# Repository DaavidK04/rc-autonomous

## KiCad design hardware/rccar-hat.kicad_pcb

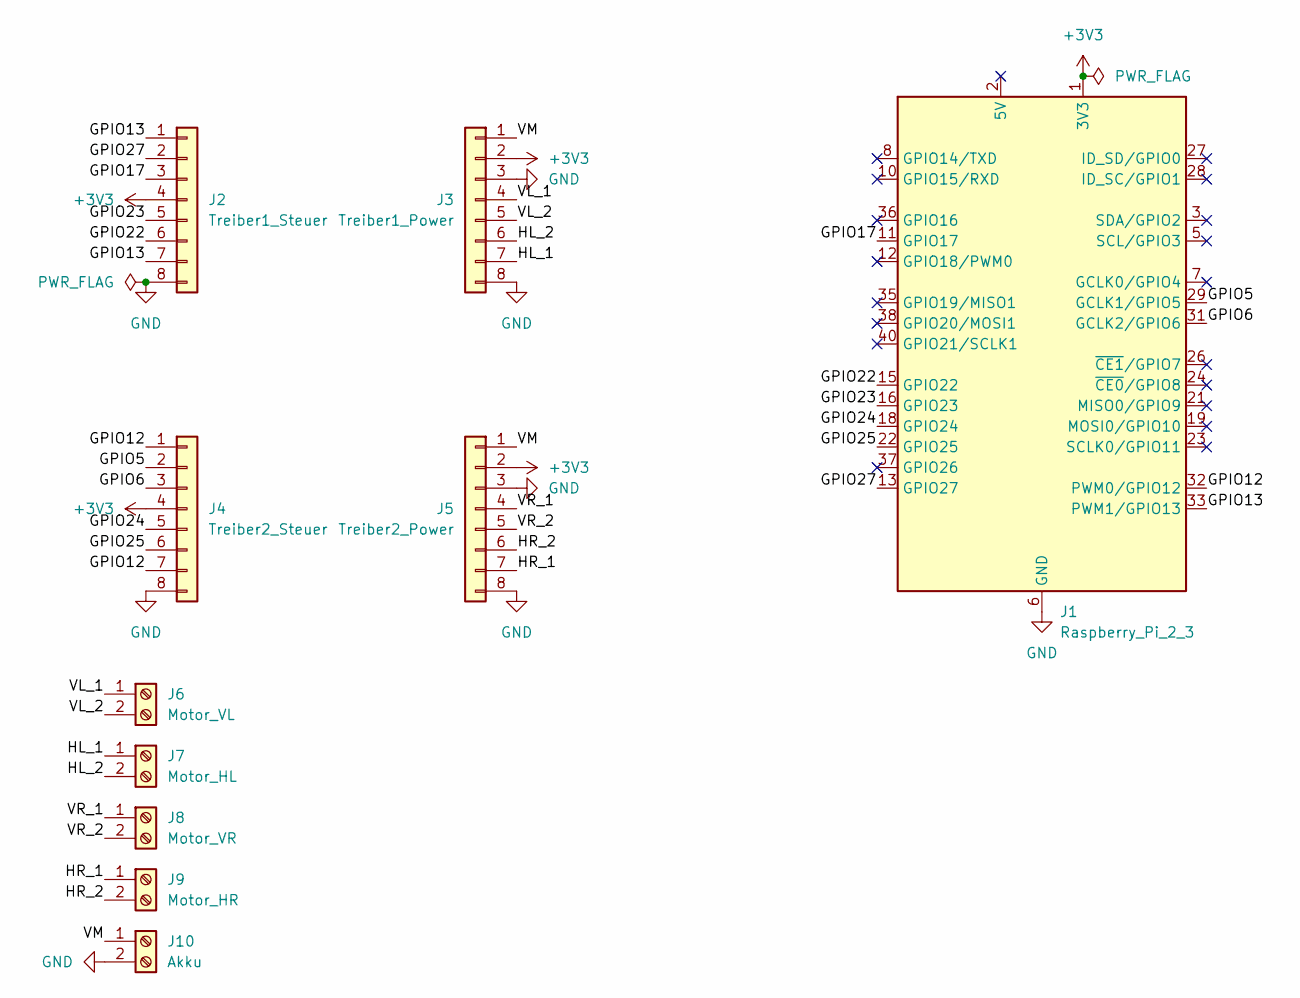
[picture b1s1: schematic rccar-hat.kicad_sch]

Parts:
J1: Raspberry_Pi_2_3; PinSocket_2x20_P2.54mm_Vertical
J2: Treiber1_Steuer; PinSocket_1x08_P2.54mm_Vertical
J3: Treiber1_Power; PinSocket_1x08_P2.54mm_Vertical
J4: Treiber2_Steuer; PinSocket_1x08_P2.54mm_Vertical
J5: Treiber2_Power; PinSocket_1x08_P2.54mm_Vertical
J6: Motor_VL; TerminalBlock_Phoenix_PT-1,5-2-3.5-H_1x02_P3.50mm_Horizontal
J7: Motor_HL; TerminalBlock_Phoenix_PT-1,5-2-3.5-H_1x02_P3.50mm_Horizontal
J8: Motor_VR; TerminalBlock_Phoenix_PT-1,5-2-3.5-H_1x02_P3.50mm_Horizontal
J9: Motor_HR; TerminalBlock_Phoenix_PT-1,5-2-3.5-H_1x02_P3.50mm_Horizontal
J10: Akku; TerminalBlock_Phoenix_PT-1,5-2-3.5-H_1x02_P3.50mm_Horizontal

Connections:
+3V3: J1.1 (3V3), J1.17 (3V3), J2.4, J3.2, J4.4, J5.2
/GPIO5: J1.29 (GCLK1/GPIO5), J4.2
/GPIO6: J1.31 (GCLK2/GPIO6), J4.3
/GPIO12: J1.32 (PWM0/GPIO12), J4.1, J4.7
/GPIO13: J1.33 (PWM1/GPIO13), J2.1, J2.7
/GPIO17: J1.11 (GPIO17), J2.3
/GPIO22: J1.15 (GPIO22), J2.6
/GPIO23: J1.16 (GPIO23), J2.5
/GPIO24: J1.18 (GPIO24), J4.5
/GPIO25: J1.22 (GPIO25), J4.6
/GPIO27: J1.13 (GPIO27), J2.2
/HL_1: J3.7, J7.1
/HL_2: J3.6, J7.2
/HR_1: J5.7, J9.1
/HR_2: J5.6, J9.2
/VL_1: J3.4, J6.1
/VL_2: J3.5, J6.2
/VM: J3.1, J5.1, J10.1
/VR_1: J5.4, J8.1
/VR_2: J5.5, J8.2
GND: J1.6 (GND), J1.9 (GND), J1.14 (GND), J1.20 (GND), J1.25 (GND), J1.30 (GND), J1.34 (GND), J1.39 (GND), J2.8, J3.3, J3.8, J4.8, J5.3, J5.8, J10.2

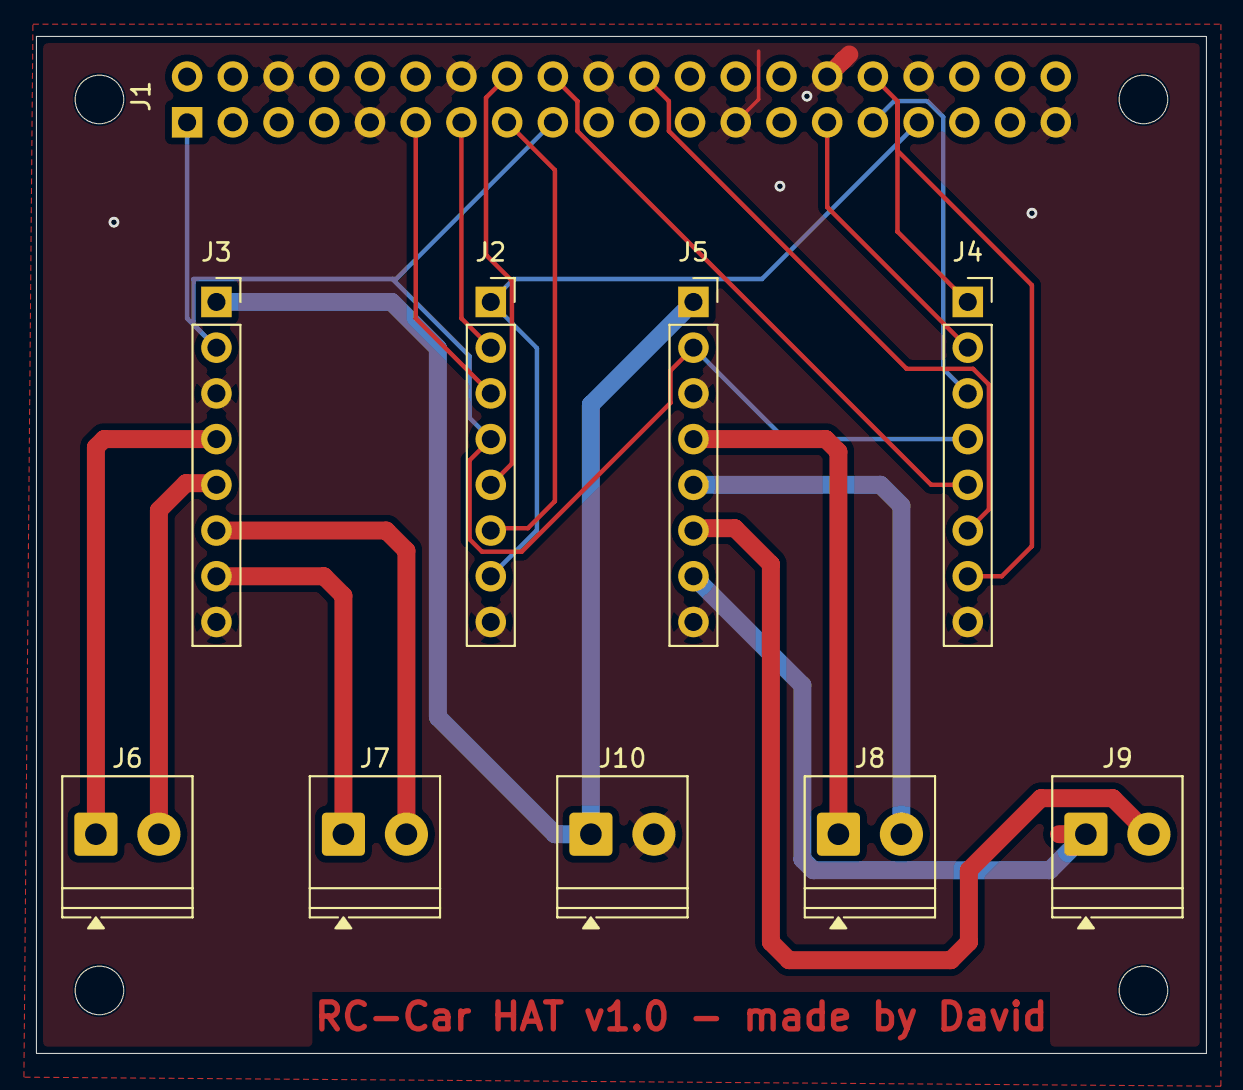
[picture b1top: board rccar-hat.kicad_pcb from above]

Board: 2 copper layers, 65.0 x 56.5 mm, 10 parts (1 on the bottom side), 21 nets.

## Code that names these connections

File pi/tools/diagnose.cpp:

// motor_diagnose.cpp
// Testet jeden Motor einzeln – damit wir wissen welcher Pin welche Seite ist
// Kompilieren: g++ motor_diagnose.cpp -o motor_diagnose -lpigpio -lpthread
// Starten:     sudo ./motor_diagnose

#include <iostream>
#include <pigpio.h>

const int LF_IN1 = 17, LF_IN2 = 27;   // "Vorne Links"
const int LR_IN1 = 23, LR_IN2 = 22;   // "Hinten Links"
const int RF_IN1 = 24, RF_IN2 = 25;   // "Hinten Rechts"
const int RR_IN1 = 6,  RR_IN2 = 5;    // "Vorne Rechts"
const int PWM_A = 12;   // ehemals PWM_FRONT
const int PWM_B = 13;   // ehemals PWM_REAR

void stopAll() {
    for (int p : {LF_IN1, LF_IN2, LR_IN1, LR_IN2,
                  RF_IN1, RF_IN2, RR_IN1, RR_IN2})
        gpioWrite(p, 0);
    gpioPWM(PWM_A, 0);
    gpioPWM(PWM_B, 0);
}

void waitEnter(const std::string& msg) {
    std::cout << msg << "  → ENTER drücken\n";
    std::cin.ignore();
}

int main() {
    if (gpioInitialise() < 0) {
        std::cerr << "pigpio init fehlgeschlagen – sudo vergessen?\n";
        return 1;
    }

    for (int p : {LF_IN1, LF_IN2, LR_IN1, LR_IN2,
                  RF_IN1, RF_IN2, RR_IN1, RR_IN2, PWM_A, PWM_B})
        gpioSetMode(p, PI_OUTPUT);

    stopAll();

    std::cout << "=== MOTOR DIAGNOSE ===\n";
    std::cout << "Notiere dir bei jedem Test WELCHER Motor dreht und in welche Richtung.\n\n";

    // ── Test 1: LF (GPIO17/27) mit PWM_A ──
    waitEnter("TEST 1: LF_IN1=17 + LF_IN2=27 vorwärts, PWM_A=12");
    gpioWrite(LF_IN1, 1); gpioWrite(LF_IN2, 0);
    gpioPWM(PWM_A, 180);
    waitEnter("  Welcher Motor dreht? Vorwärts oder rückwärts?");
    stopAll(); gpioDelay(500000);

    // ── Test 2: LF mit PWM_B ──
    waitEnter("TEST 2: LF_IN1=17 + LF_IN2=27 vorwärts, PWM_B=13");
    gpioWrite(LF_IN1, 1); gpioWrite(LF_IN2, 0);
    gpioPWM(PWM_B, 180);
    waitEnter("  Welcher Motor dreht? Vorwärts oder rückwärts?");
    stopAll(); gpioDelay(500000);

    // ── Test 3: LR (GPIO23/22) mit PWM_A ──
    waitEnter("TEST 3: LR_IN1=23 + LR_IN2=22 vorwärts, PWM_A=12");
    gpioWrite(LR_IN1, 1); gpioWrite(LR_IN2, 0);
    gpioPWM(PWM_A, 180);
    waitEnter("  Welcher Motor dreht?");
    stopAll(); gpioDelay(500000);

    // ── Test 4: LR mit PWM_B ──
    waitEnter("TEST 4: LR_IN1=23 + LR_IN2=22 vorwärts, PWM_B=13");
    gpioWrite(LR_IN1, 1); gpioWrite(LR_IN2, 0);
    gpioPWM(PWM_B, 180);
    waitEnter("  Welcher Motor dreht?");
    stopAll(); gpioDelay(500000);

    // ── Test 5: RF (GPIO24/25) mit PWM_A ──
    waitEnter("TEST 5: RF_IN1=24 + RF_IN2=25 vorwärts, PWM_A=12");
    gpioWrite(RF_IN1, 1); gpioWrite(RF_IN2, 0);
    gpioPWM(PWM_A, 180);
    waitEnter("  Welcher Motor dreht?");
    stopAll(); gpioDelay(500000);

    // ── Test 6: RF mit PWM_B ──
    waitEnter("TEST 6: RF_IN1=24 + RF_IN2=25 vorwärts, PWM_B=13");
    gpioWrite(RF_IN1, 1); gpioWrite(RF_IN2, 0);
    gpioPWM(PWM_B, 180);
    waitEnter("  Welcher Motor dreht?");
    stopAll(); gpioDelay(500000);

    // ── Test 7: RR (GPIO6/5) mit PWM_A ──
    waitEnter("TEST 7: RR_IN1=6 + RR_IN2=5 vorwärts, PWM_A=12");
    gpioWrite(RR_IN1, 1); gpioWrite(RR_IN2, 0);
    gpioPWM(PWM_A, 180);
    waitEnter("  Welcher Motor dreht?");
    stopAll(); gpioDelay(500000);

    // ── Test 8: RR mit PWM_B ──
    waitEnter("TEST 8: RR_IN1=6 + RR_IN2=5 vorwärts, PWM_B=13");
    gpioWrite(RR_IN1, 1); gpioWrite(RR_IN2, 0);
    gpioPWM(PWM_B, 180);
    waitEnter("  Welcher Motor dreht?");
    stopAll();

    std::cout << "\n=== DIAGNOSE ABGESCHLOSSEN ===\n";
    std::cout << "Schick mir die Ergebnisse und ich fixe den finalen Code!\n";

    gpioTerminate();
    return 0;
}
